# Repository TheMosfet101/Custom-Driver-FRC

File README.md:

# Custom-Driver-FRC
A Custom Circuit Board for the FIRST Robotics Competition, utilizing the new SystemCore as it features 5 SL Molex Connectors for receiving digital pins, a screw terminal for power input from the Mini Power Module, a shift register + 555 timer to send signals/update them, and LED indicators to represent the different sub-systems of a robot.

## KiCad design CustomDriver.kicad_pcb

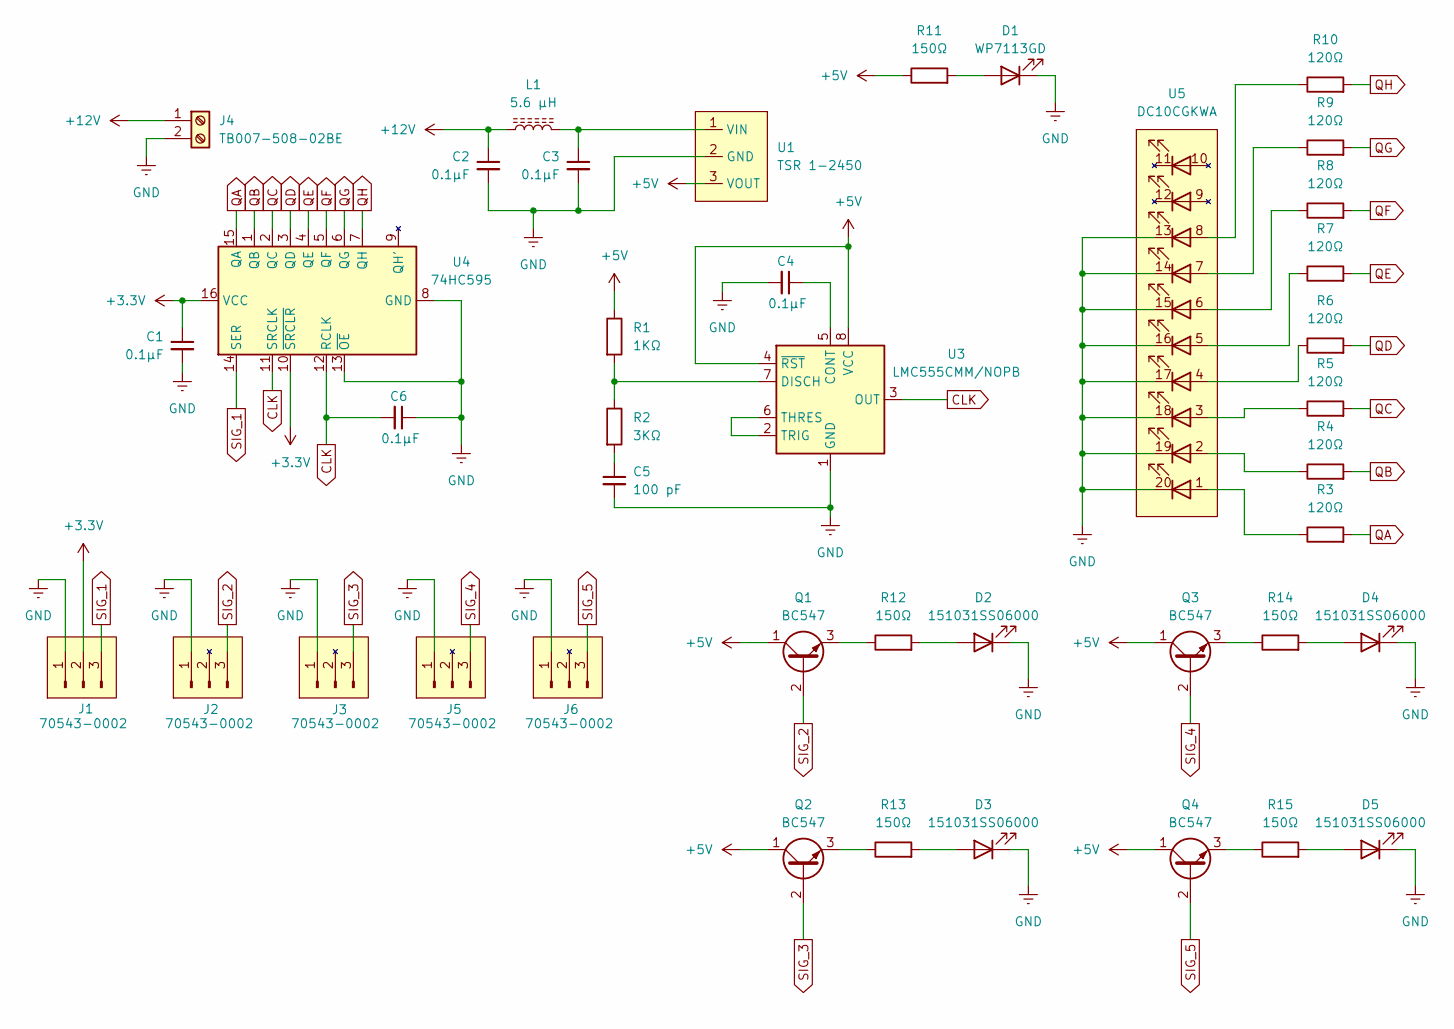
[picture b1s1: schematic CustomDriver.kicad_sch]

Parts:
C1, C2, C3, C4, C6: 0.1µF; 0.1µF Cap SMD
C5: 100 pF; 100pF Cap SMD
D1: WP7113GD; Green LED
D2, D3, D4, D5: 151031SS06000; Red LED
J1, J2, J3, J5, J6: 70543-0002; MOLEX_70543-0002
J4: TB007-508-02BE
L1: 5.6 µH; 5.6µH Inductor
Q1, Q2, Q3, Q4: BC547; TO-92_Inline
R1: 1KΩ; 1KΩ Resistor SMD
R2: 3KΩ; 3KΩ Resistor SMD
R3, R4, R5, R6, R7, R8, R9, R10: 120Ω; 120Ω Resistor SMD
R11, R12, R13, R14, R15: 150Ω; 150Ω Resistor
U1: TSR 1-2450
U3: LMC555CMM/NOPB; VSSOP-8_3x3mm_P0.65mm
U4: 74HC595
U5: DC10CGKWA

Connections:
+5V: Q1.1 (C), Q2.1 (C), Q3.1 (C), Q4.1 (C), R1.1, R11.1, U1.3 (VOUT), U3.4 (~RST), U3.8 (VCC)
+12V: C2.1, J4.1, L1.1
CLK: C6.2, U3.3 (OUT), U4.11 (SRCLK), U4.12 (RCLK)
unnamed: C5.1, R2.2
unnamed: D1.2 (A), R11.2
unnamed: D2.2 (A), R12.2
unnamed: D3.2 (A), R13.2
unnamed: D4.2 (A), R14.2
unnamed: D5.2 (A), R15.2
unnamed: Q1.3 (E), R12.1
unnamed: Q2.3 (E), R13.1
unnamed: Q3.3 (E), R14.1
unnamed: Q4.3 (E), R15.1
unnamed: R3.1, U5.1 (A)
unnamed: R4.1, U5.2 (A)
unnamed: R5.1, U5.3 (A)
unnamed: R6.1, U5.4 (A)
unnamed: R7.1, U5.5 (A)
unnamed: R8.1, U5.6 (A)
unnamed: R9.1, U5.7 (A)
unnamed: R10.1, U5.8 (A)
unnamed: C3.1, L1.2, U1.1 (VIN)
unnamed: C4.1, U3.5 (CONT)
unnamed: R1.2, R2.1, U3.7 (DISCH)
unnamed: U3.2 (TRIG), U3.6 (THRES)
QA: R3.2, U4.15 (QA)
QB: R4.2, U4.1 (QB)
QC: R5.2, U4.2 (QC)
QD: R6.2, U4.3 (QD)
QE: R7.2, U4.4 (QE)
QF: R8.2, U4.5 (QF)
QG: R9.2, U4.6 (QG)
QH: R10.2, U4.7 (QH)
SIG_1: J1.3, U4.14 (SER)
SIG_2: J2.3, Q1.2 (B)
SIG_3: J3.3, Q2.2 (B)
SIG_4: J5.3, Q3.2 (B)
SIG_5: J6.3, Q4.2 (B)

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
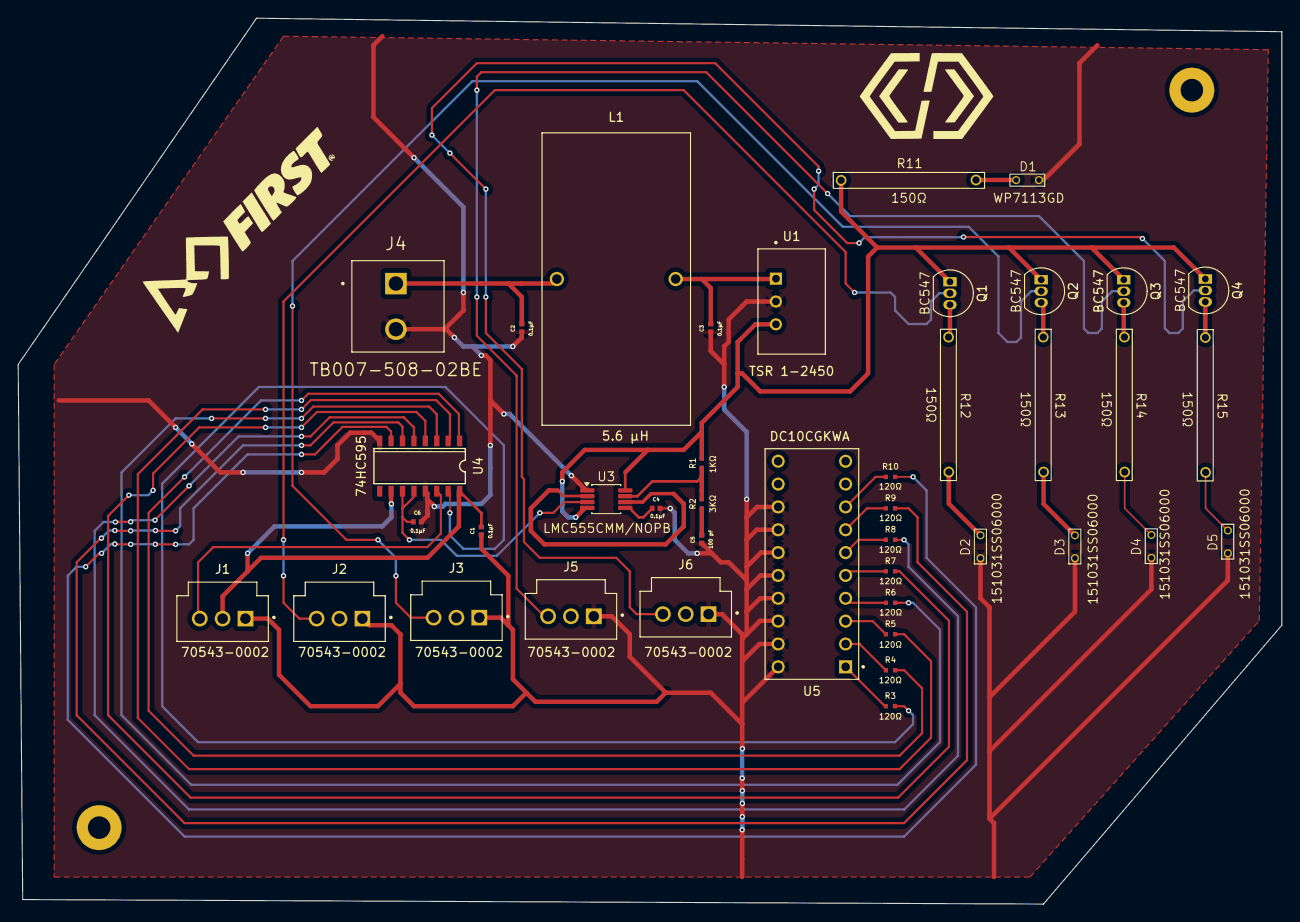
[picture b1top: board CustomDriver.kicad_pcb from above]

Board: 2 copper layers, 140.5 x 98.5 mm, 41 parts (0 on the bottom side), 40 nets.

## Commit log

2026-05-02 Add images to README for better visualization
    Added images to enhance documentation with visual references.
2026-05-02 Add new image to README and remove old one
